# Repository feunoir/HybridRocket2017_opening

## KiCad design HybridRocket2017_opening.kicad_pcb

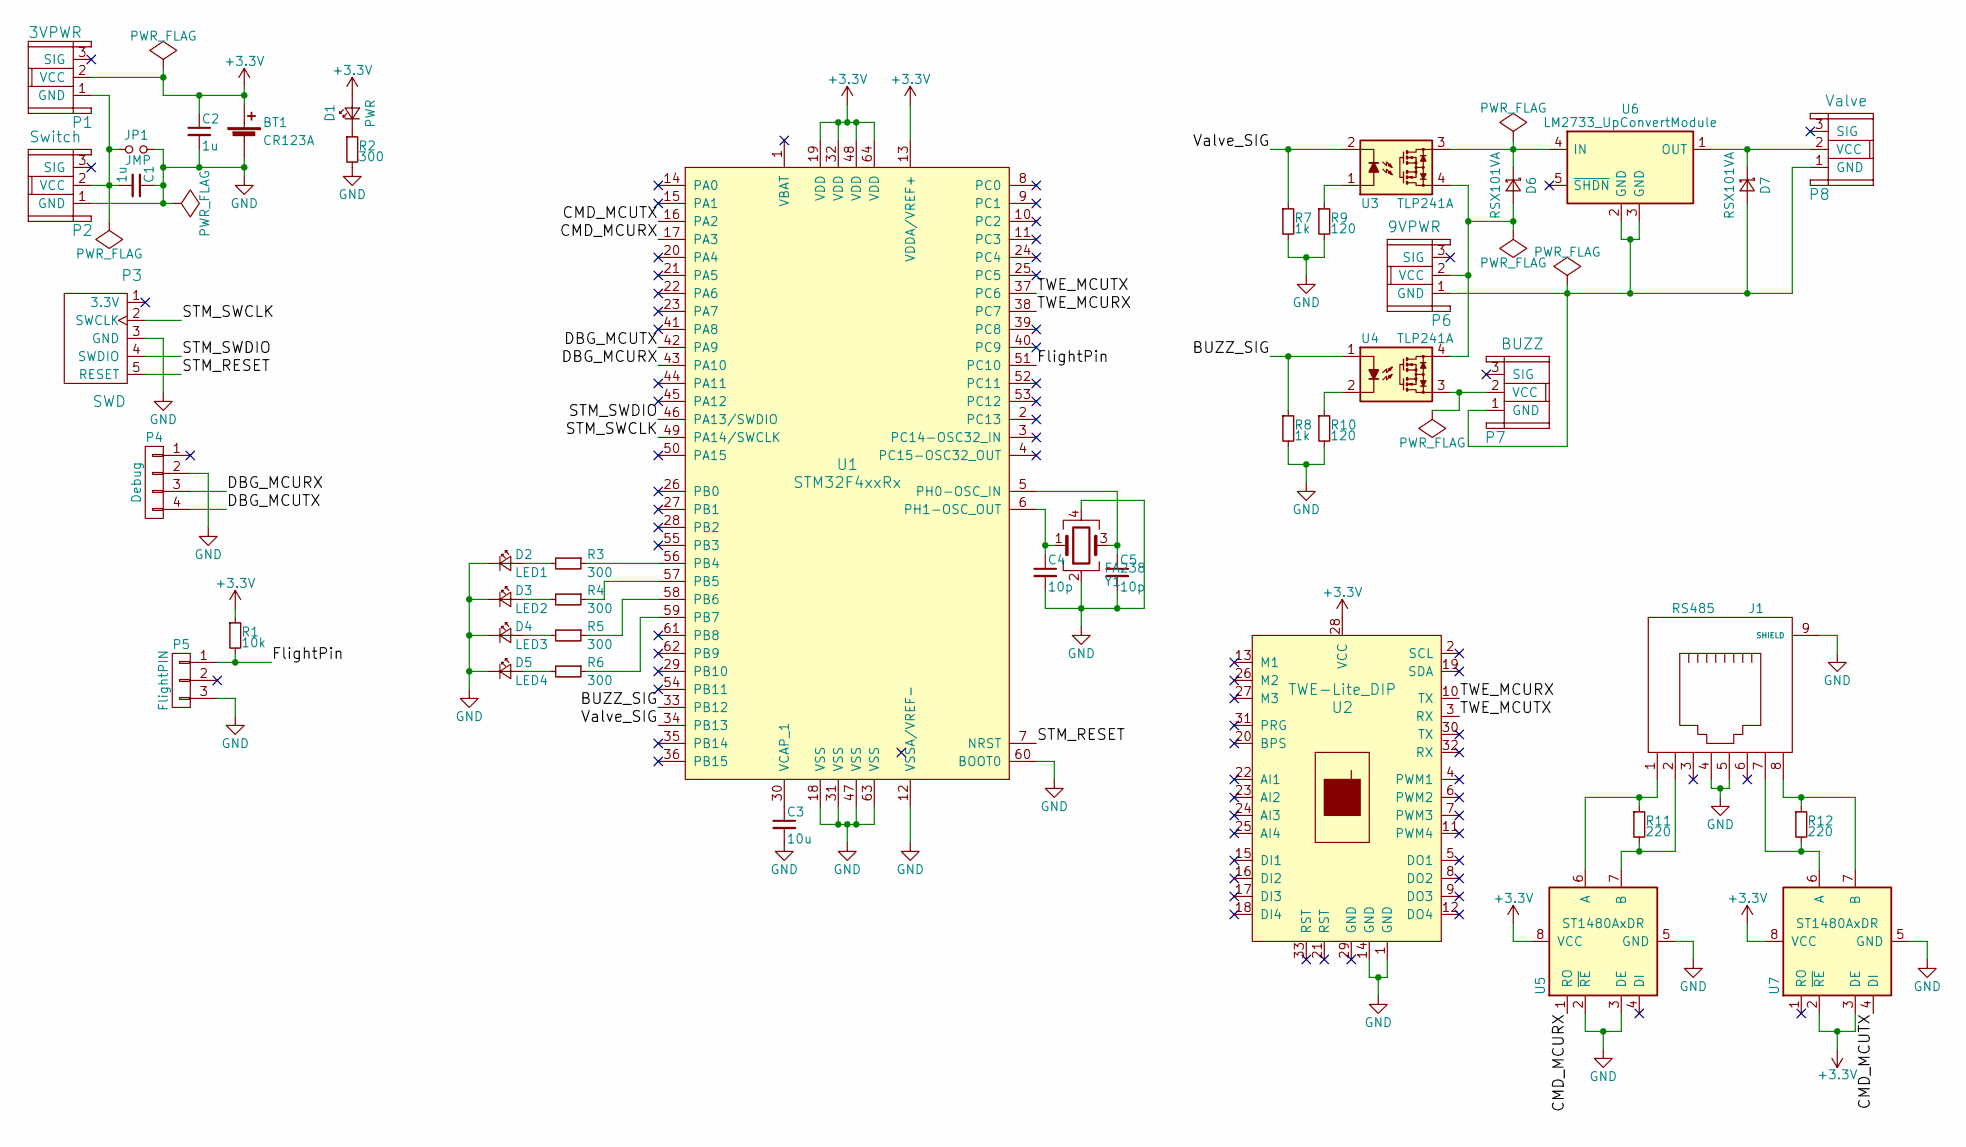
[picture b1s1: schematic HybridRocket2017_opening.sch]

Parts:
BT1: CR123A; BHC-CR123A
C1, C2: 1u; C_0805
C3: 10u; C_0805
C4, C5: 10p; C_0603
D1: PWR; LED_0603
D2: LED1; LED_0603
D3: LED2; LED_0603
D4: LED3; LED_0603
D5: LED4; LED_0603
D6, D7: RSX101VA; D_TUMD2
J1: RS485; 7810-8P8C
JP1: JMP; Jumper_NO
P1: 3VPWR; DF1E-3P
P2: Switch; DF1E-3P_Straight
P3: SWD; DF1E-5P_Straight
P4: Debug; Pin_Header_Straight_1x04_Pitch2.54mm
P5: FlightPIN; DF1E-3P_Straight
P6: 9VPWR; DF1E-3P
P7: BUZZ; DF1E-3P
P8: Valve; DF1E-3P
R1: 10k; R_0603_HandSoldering
R2, R3, R4, R5, R6: 300; R_0603_HandSoldering
R7, R8: 1k; R_0603_HandSoldering
R9, R10: 120; R_0603_HandSoldering
R11, R12: 220; R_0603_HandSoldering
U1: STM32F4xxRx; LQFP-64_10x10mm_Pitch0.5mm
U2: TWE-Lite_DIP; TWE-Lite_DIP_28P
U3, U4: TLP241A; DIP-4_W7.62mm_LongPads
U5, U7: ST1480AxDR; SOIC-8_3.9x4.9mm_Pitch1.27mm
U6: LM2733_UpConvertModule
Y1: FA238; Crystal_SMD_SeikoEpson_FA238-4pin_3.2x2.5mm_HandSoldering

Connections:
+3V3: BT1.1 (+), C2.1, D1.2 (A), P1.2 (VCC), R1.1, U1.13 (VDDA/VREF+), U1.19 (VDD), U1.32 (VDD), U1.48 (VDD), U1.64 (VDD), U2.28 (VCC), U5.8 (VCC), U7.2 (~RE~), U7.3 (DE), U7.8 (VCC)
/BUZZ_SIG: R8.1, U1.33 (PB12), U4.1
/CMD_MCURX: U1.17 (PA3), U5.1 (RO)
/CMD_MCUTX: U1.16 (PA2), U7.4 (DI)
/DBG_MCURX: P4.3, U1.43 (PA10)
/DBG_MCUTX: P4.4, U1.42 (PA9)
/FlightPin: P5.1, R1.2, U1.51 (PC10)
/STM_RESET: P3.5 (RESET), U1.7 (NRST)
/STM_SWCLK: P3.2 (SWCLK), U1.49 (PA14/SWCLK)
/STM_SWDIO: P3.4 (SWDIO), U1.46 (PA13/SWDIO)
/TWE_MCURX: U1.38 (PC7), U2.10 (TX)
/TWE_MCUTX: U1.37 (PC6), U2.3 (RX)
/Valve_SIG: R7.1, U1.34 (PB13), U3.2
GND: BT1.2 (-), C1.1, C2.2, C3.2, C4.2, C5.2, D2.1 (K), D3.1 (K), D4.1 (K), D5.1 (K), J1.4, J1.5, J1.9 (SHIELD), JP1.2, P2.1 (GND), P3.3 (GND), P4.2, P5.3, R2.2, R7.2, R8.2, R9.2, R10.2, U1.12 (VSSA/VREF-), U1.18 (VSS), U1.31 (VSS), U1.47 (VSS), U1.60 (BOOT0), U1.63 (VSS), U2.1 (GND), U2.14 (GND), U5.2 (~RE~), U5.3 (DE), U5.5 (GND), U7.5 (GND), Y1.2, Y1.4
unnamed: C1.2, JP1.1, P1.1 (GND), P2.2 (VCC)
unnamed: C3.1, U1.30 (VCAP_1)
unnamed: C4.1, U1.6 (PH1-OSC_OUT), Y1.1
unnamed: C5.1, U1.5 (PH0-OSC_IN), Y1.3
unnamed: D1.1 (K), R2.1
unnamed: D2.2 (A), R3.2
unnamed: D3.2 (A), R4.2
unnamed: D4.2 (A), R5.2
unnamed: D5.2 (A), R6.2
unnamed: D6.1 (K), U3.3, U6.4 (IN)
unnamed: D6.2 (A), P6.2 (VCC), U3.4, U4.4
unnamed: D7.1 (K), P8.2 (VCC), U6.1 (OUT)
unnamed: D7.2 (A), P6.1 (GND), P7.1 (GND), P8.1 (GND), U6.2 (GND), U6.3 (GND)
unnamed: J1.1, R11.1, U5.6 (A)
unnamed: J1.2, R11.2, U5.7 (B)
unnamed: J1.7, R12.2, U7.6 (A)
unnamed: J1.8, R12.1, U7.7 (B)
unnamed: P7.2 (VCC), U4.3
unnamed: R3.1, U1.56 (PB4)
unnamed: R4.1, U1.57 (PB5)
unnamed: R5.1, U1.58 (PB6)
unnamed: R6.1, U1.59 (PB7)
unnamed: R9.1, U3.1
unnamed: R10.1, U4.2

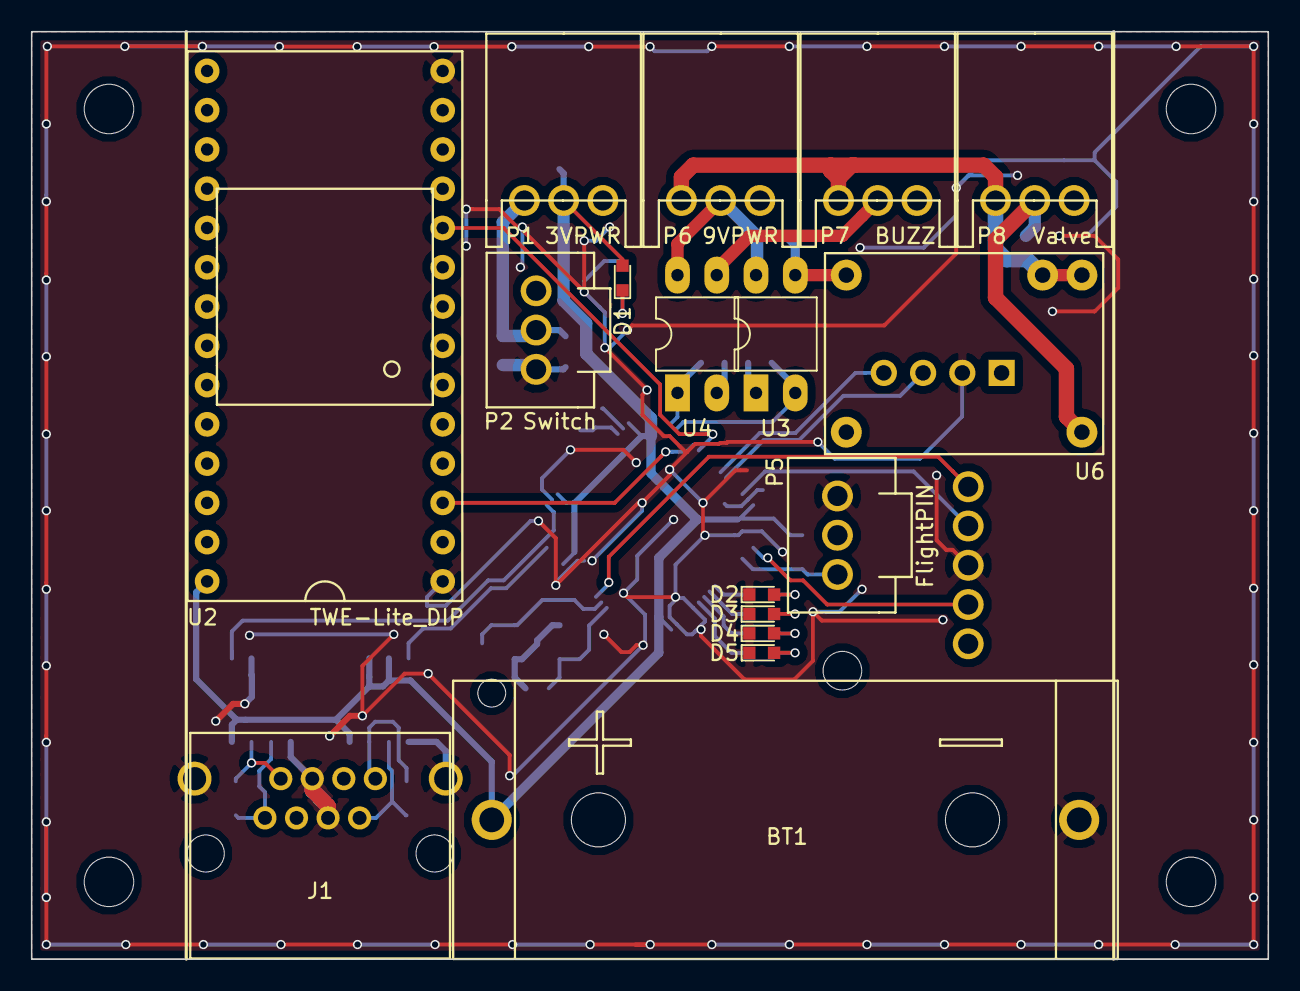
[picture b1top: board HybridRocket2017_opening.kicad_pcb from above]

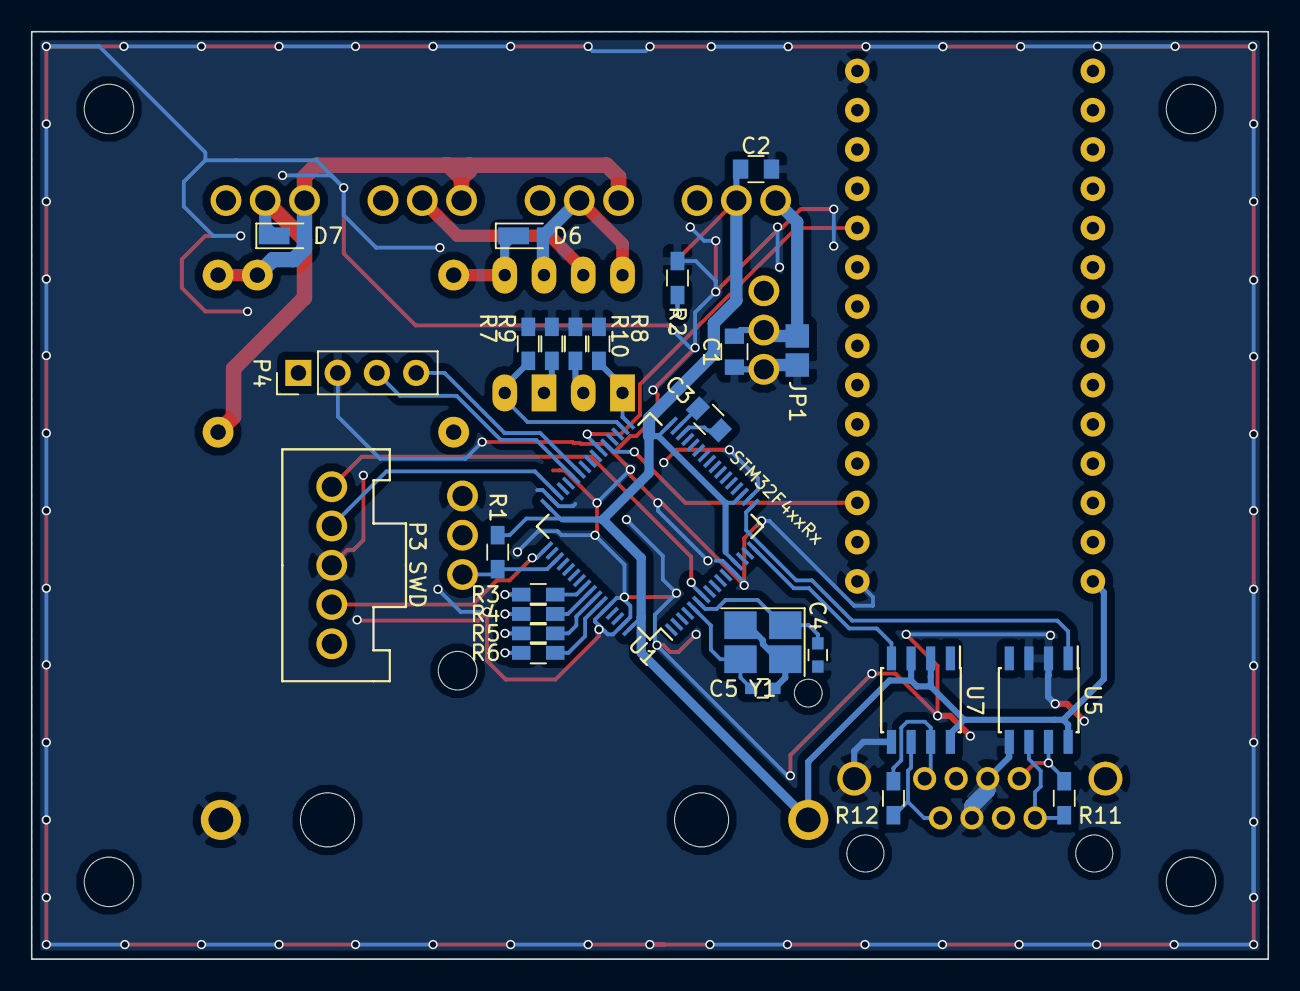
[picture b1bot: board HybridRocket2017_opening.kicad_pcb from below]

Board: 2 copper layers, 80.0 x 60.0 mm, 43 parts (26 on the bottom side), 38 nets.

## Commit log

2017-03-10 :confetti_ball: Added .gitattributes & .gitignore files
2017-03-10 firstcommit
2017-07-02 製作中にコミットするの忘れてた
